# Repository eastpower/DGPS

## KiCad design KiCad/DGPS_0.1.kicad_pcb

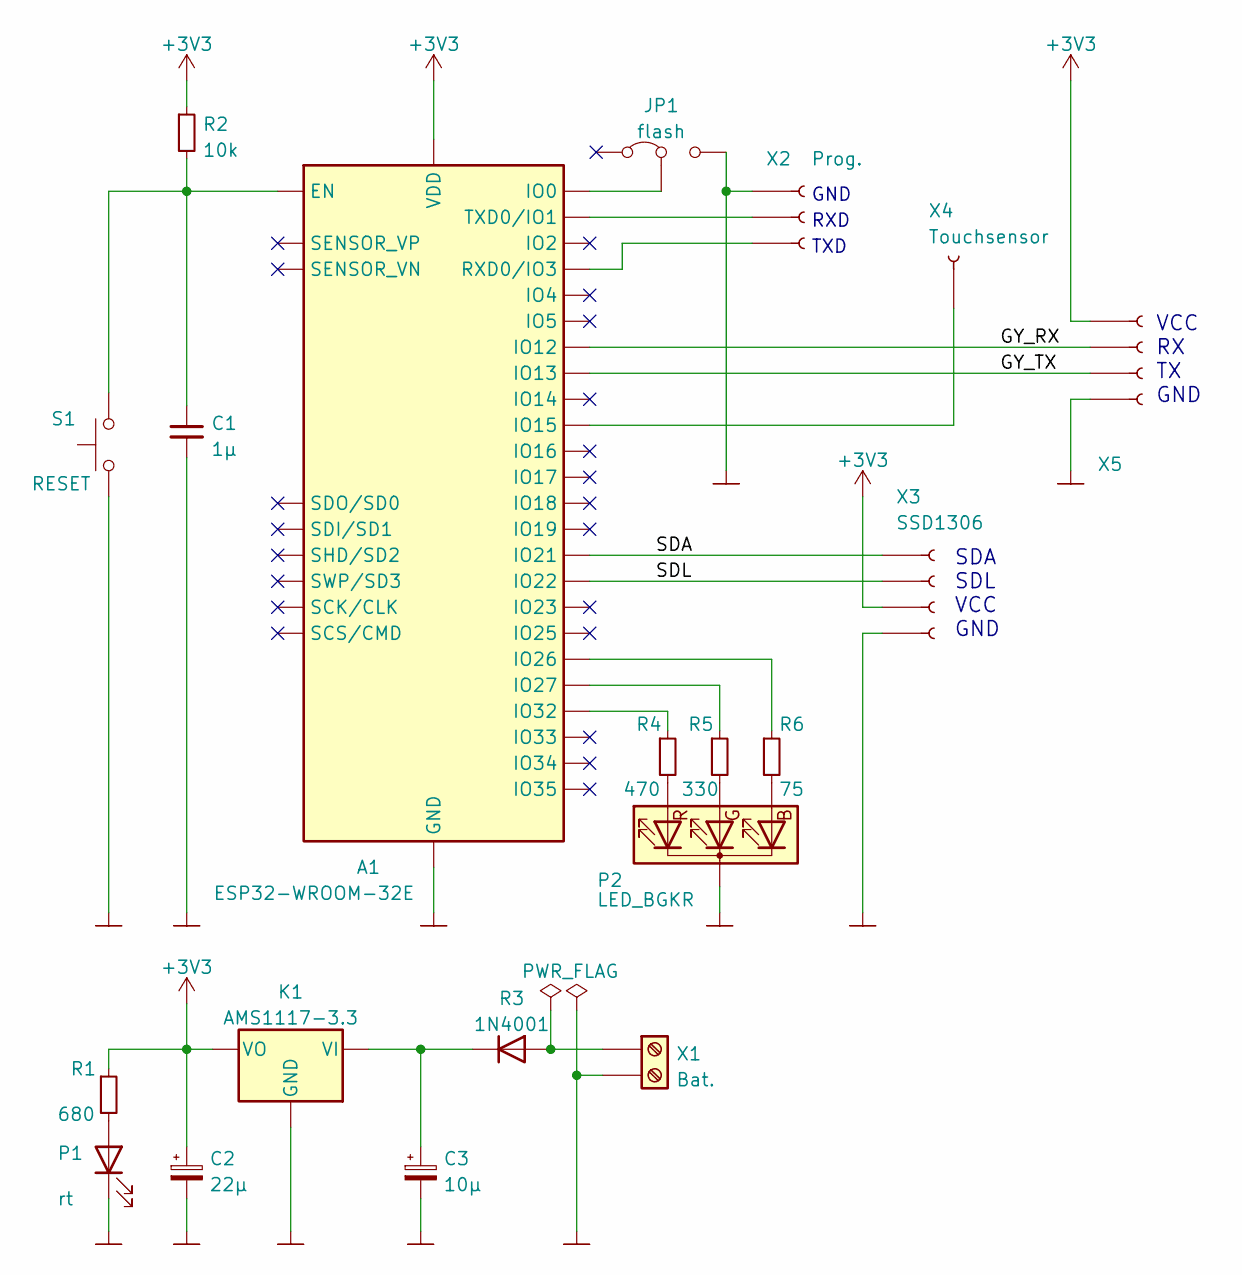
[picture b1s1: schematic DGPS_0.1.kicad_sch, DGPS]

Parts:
A1: ESP32-WROOM-32E; ESP32-WROOM-32
C1: 1µ; C_1206_3216Metric_Pad1.33x1.80mm_HandSolder
C2: 22µ; CP_EIA-7360-38_Kemet-E_Pad2.25x4.25mm_HandSolder
C3: 10µ; CP_EIA-7360-38_Kemet-E_Pad2.25x4.25mm_HandSolder
JP1: flash; PinHeader_1x03_P2.54mm_Vertical
K1: AMS1117-3.3; SOT-223-3_TabPin2
P1: rt; LED_D3.0mm
P2: LED_BGKR; LED_D5.0mm-4_RGB
R1: 680; R_1206_3216Metric_Pad1.30x1.75mm_HandSolder
R2: 10k; R_1206_3216Metric_Pad1.30x1.75mm_HandSolder
R3: 1N4001; D_DO-41_SOD81_P10.16mm_Horizontal
R4: 470; R_1206_3216Metric_Pad1.30x1.75mm_HandSolder
R5: 330; R_1206_3216Metric_Pad1.30x1.75mm_HandSolder
R6: 75; R_1206_3216Metric_Pad1.30x1.75mm_HandSolder
S1: RESET; SW_TH_Tactile_Omron_B3F-10xx
X1: Bat.; TerminalBlock_bornier-2_P5.08mm
X2: Prog.; PinSocket_1x03_P2.54mm_Vertical
X3: SSD1306; PinSocket_1x04_P2.54mm_Vertical
X4: Touchsensor; PinHeader_1x01_P2.54mm_Vertical
X5: PinSocket_1x04_P2.54mm_Horizontal

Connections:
+3V3: A1.2 (VDD), C2.1, K1.2 (VO), R1.1, R2.1, X3.3, X5.1
/GY_RX: A1.14 (IO12), X5.2
/GY_TX: A1.16 (IO13), X5.3
/SDA: A1.33 (IO21), X3.1
/SDL: A1.36 (IO22), X3.2
GND: A1.1 (GND), A1.15 (GND), A1.38 (GND), A1.39 (GND), C1.2, C2.2, C3.2, JP1.3 (B), K1.1 (GND), P1.1 (K), P2.3 (K), S1.1, X1.2, X2.1, X3.4, X5.4
unnamed: A1.3 (EN), C1.1, R2.2, S1.2
unnamed: A1.8 (IO32), R4.1
unnamed: A1.11 (IO26), R6.1
unnamed: A1.12 (IO27), R5.1
unnamed: A1.23 (IO15), X4.1
unnamed: A1.25 (IO0), JP1.2 (C)
unnamed: A1.34 (RXD0/IO3), X2.3
unnamed: A1.35 (TXD0/IO1), X2.2
unnamed: C3.1, K1.3 (VI), R3.1 (K)
unnamed: P1.2 (A), R1.2
unnamed: P2.1 (BA), R6.2
unnamed: P2.2 (GA), R5.2
unnamed: P2.4 (RA), R4.2
unnamed: R3.2 (A), X1.1

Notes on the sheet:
GND
RXD
SDA SDL VCC GND
TXD
VCC RX TX GND

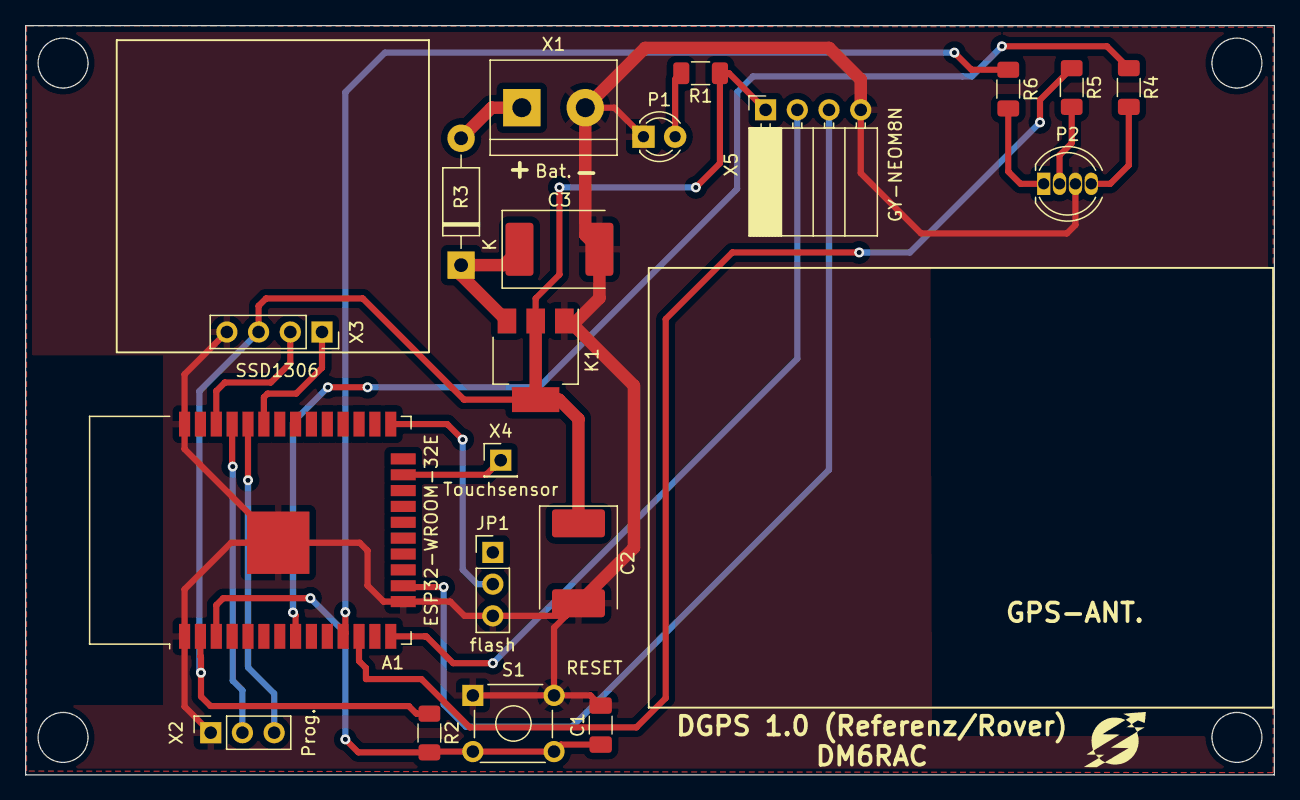
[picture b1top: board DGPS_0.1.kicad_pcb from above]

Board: 2 copper layers, 100.0 x 60.0 mm, 20 parts (0 on the bottom side), 20 nets.

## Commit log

2022-12-03 Update LICENSE
